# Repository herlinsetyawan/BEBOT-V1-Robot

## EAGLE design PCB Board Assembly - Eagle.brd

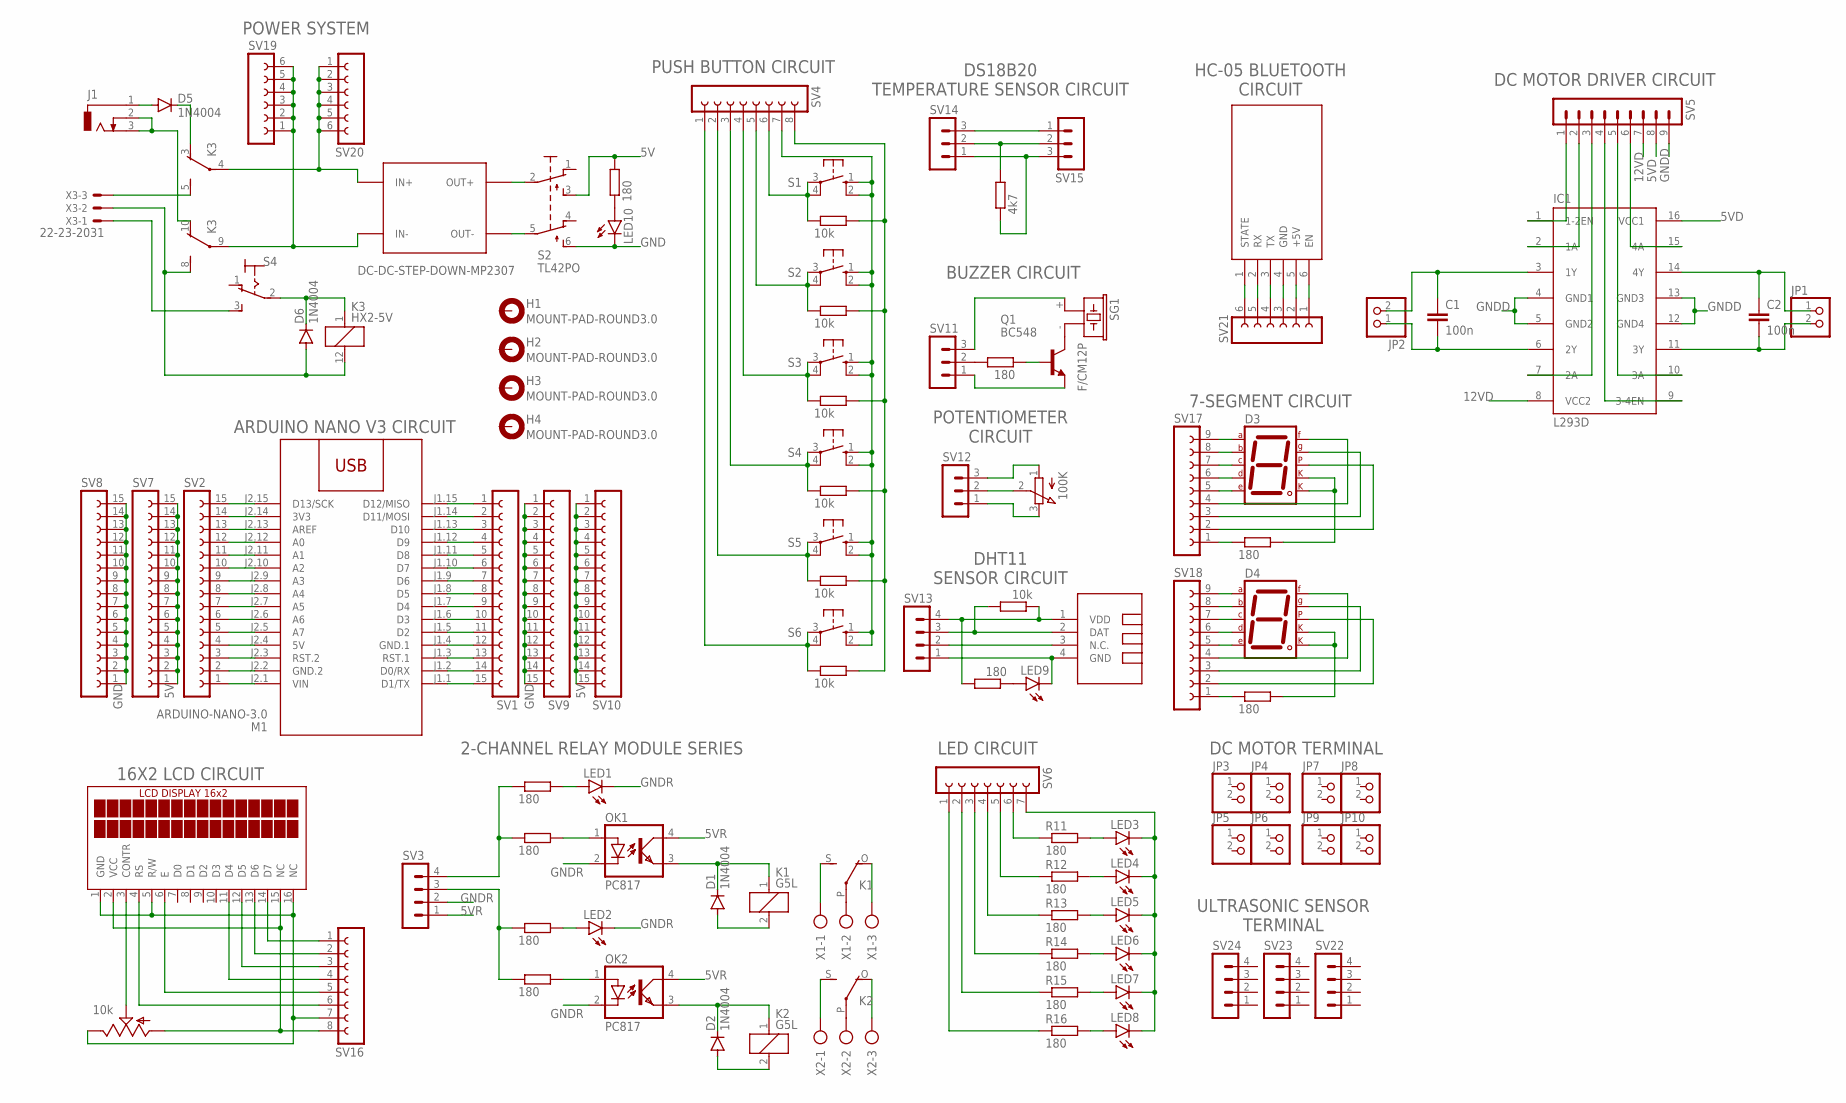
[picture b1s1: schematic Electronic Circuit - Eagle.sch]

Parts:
C1, C2: 100n; C050-024X044
D1, D2, D5, D6: 1N4004; DO41-10
D3, D4: 7SEG-CK; 7SEG-13
DIS1: TUXGR_16X2_R2
H1, H2, H3, H4: MOUNT-PAD-ROUND3.0; 3,0-PAD
IC1: L293D; DIL16
J1: DCJ0303
JP1, JP2, JP3, JP4, JP5, JP6, JP7, JP8, JP9, JP10: PINHD-1X2; 1X02
K1, K2: G5L; G5LE
K3: HX2-5V; HX
LED1, LED2, LED3, LED4, LED5, LED6, LED7, LED8, LED9, LED10: LED3MM
M1: ARDUINO-NANO-3.0
OK1, OK2: PC817; DIL04
Q1: BC548; TO92-EBC
R1, R2, R3, R4, R11, R12, R13, R14, R15, R16, R17, R20, R23, R24, R25: 180; 0204/7
R5, R6, R7, R8, R9, R10, R19: 10k; 0204/7
R18: 100K; EVUF
R21: 4k7; 0204/7
R22: 10k; CA6V
S1, S3, S5, S6, S7, S8: 10-XX; B3F-10XX
S2: TL42PO; TL4XPO
S4: M9040P
SG1: F/CM12P
SV1, SV2, SV7, SV8, SV9, SV10: FE15-1; FE15
SV3, SV13, SV22, SV23, SV24: MA04-1
SV4, SV16: FE08-1; FE08
SV5: MA09-1
SV6: FE07-1; FE07
SV11, SV12, SV14, SV15: MA03-1
SV17, SV18: FE09-1; FE09
SV19, SV20, SV21: FE06-1; FE06
U$1: TEMP-HUM-SENSOR-DHT11
U$2: WIRELESS-BLUETOOTH-HC-05
U$3: DC-DC-STEP-DOWN-MP2307
X1, X2: AK500/3
X3: 22-23-2031

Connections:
5V: R25.2, S2.3 (S), SV7.1, SV7.2, SV7.3, SV7.4, SV7.5, SV7.6, SV7.7, SV7.8, SV7.9, SV7.10, SV7.11, SV7.12, SV7.13, SV7.14, SV7.15, SV10.1, SV10.2, SV10.3, SV10.4, SV10.5, SV10.6, SV10.7, SV10.8, SV10.9, SV10.10, SV10.11, SV10.12, SV10.13, SV10.14, SV10.15
5VD: IC1.16 (VCC1), SV5.8
5VR: OK1.4 (COL), OK2.4 (COL), SV3.1
12VD: IC1.8 (VCC2), SV5.7
GND: LED10.K (C), S2.6 (S1), SV8.1, SV8.2, SV8.3, SV8.4, SV8.5, SV8.6, SV8.7, SV8.8, SV8.9, SV8.10, SV8.11, SV8.12, SV8.13, SV8.14, SV8.15, SV9.1, SV9.2, SV9.3, SV9.4, SV9.5, SV9.6, SV9.7, SV9.8, SV9.9, SV9.10, SV9.11, SV9.12, SV9.13, SV9.14, SV9.15
GNDD: IC1.4 (GND1), IC1.5 (GND2), IC1.12 (GND4), IC1.13 (GND3), SV5.9
GNDR: LED1.K (C), LED2.K (C), OK1.2 (C), OK2.2 (C), SV3.2
unnamed: M1.J2.15 (D13/SCK), SV2.15
unnamed: M1.J2.14 (3V3), SV2.14
unnamed: M1.J2.13 (AREF), SV2.13
unnamed: M1.J2.12 (A0), SV2.12
unnamed: M1.J2.11 (A1), SV2.11
unnamed: M1.J2.10 (A2), SV2.10
unnamed: M1.J2.9 (A3), SV2.9
unnamed: M1.J2.8 (A4), SV2.8
unnamed: M1.J2.7 (A5), SV2.7
unnamed: M1.J2.6 (A6), SV2.6
unnamed: M1.J2.5 (A7), SV2.5
unnamed: M1.J2.4 (5V), SV2.4
unnamed: M1.J2.3 (RST.2), SV2.3
unnamed: M1.J2.2 (GND.2), SV2.2
unnamed: M1.J2.1 (VIN), SV2.1
unnamed: M1.J1.1 (D1/TX), SV1.15
unnamed: M1.J1.2 (D0/RX), SV1.14
unnamed: M1.J1.3 (RST.1), SV1.13
unnamed: M1.J1.4 (GND.1), SV1.12
unnamed: M1.J1.5 (D2), SV1.11
unnamed: M1.J1.6 (D3), SV1.10
unnamed: M1.J1.7 (D4), SV1.9
unnamed: M1.J1.8 (D5), SV1.8
unnamed: M1.J1.9 (D6), SV1.7
unnamed: M1.J1.10 (D7), SV1.6
unnamed: M1.J1.11 (D8), SV1.5
unnamed: M1.J1.12 (D9), SV1.4
unnamed: M1.J1.13 (D10), SV1.3
unnamed: M1.J1.14 (D11/MOSI), SV1.2
unnamed: M1.J1.15 (D12/MISO), SV1.1
unnamed: OK1.1 (A), R1.2
unnamed: D1.C, K1.1, OK1.3 (EMIT)
unnamed: D1.A, K1.2
unnamed: K1.S, X1.1
unnamed: K1.P, X1.2
unnamed: K1.O, X1.3
unnamed: OK2.1 (A), R2.2
unnamed: D2.C, K2.1, OK2.3 (EMIT)
unnamed: D2.A, K2.2
unnamed: K2.S, X2.1
unnamed: K2.P, X2.2
unnamed: K2.O, X2.3
unnamed: R2.1, R4.1, SV3.3
unnamed: R1.1, R3.1, SV3.4
unnamed: LED1.A, R3.2
unnamed: LED2.A, R4.2
unnamed: C1.1, IC1.3 (1Y), JP2.2
unnamed: C1.2, IC1.6 (2Y), JP2.1
unnamed: C2.1, IC1.14 (4Y), JP1.1
unnamed: C2.2, IC1.11 (3Y), JP1.2
unnamed: IC1.1 (1-2EN), SV5.1
unnamed: IC1.2 (1A), SV5.2
unnamed: IC1.7 (2A), SV5.3
unnamed: IC1.9 (3-4EN), SV5.4
unnamed: IC1.10 (3A), SV5.5
unnamed: IC1.15 (4A), SV5.6
unnamed: R5.1, S1.3, S1.4 (P1), SV4.6
unnamed: R6.1, S3.3, S3.4 (P1), SV4.5
unnamed: R7.1, S5.3, S5.4 (P1), SV4.4
unnamed: R8.1, S6.3, S6.4 (P1), SV4.3
unnamed: R9.1, S7.3, S7.4 (P1), SV4.2
unnamed: R10.1, S8.3, S8.4 (P1), SV4.1
unnamed: S1.1 (S), S1.2 (S1), S3.1 (S), S3.2 (S1), S5.1 (S), S5.2 (S1), S6.1 (S), S6.2 (S1), S7.1 (S), S7.2 (S1), S8.1 (S), S8.2 (S1), SV4.7
unnamed: R5.2, R6.2, R7.2, R8.2, R9.2, R10.2, SV4.8
unnamed: LED3.A, R11.2
unnamed: LED4.A, R12.2
unnamed: LED5.A, R13.2
unnamed: LED6.A, R14.2
unnamed: LED7.A, R15.2
unnamed: LED8.A, R16.2
unnamed: LED3.K (C), LED4.K (C), LED5.K (C), LED6.K (C), LED7.K (C), LED8.K (C), SV6.7
unnamed: R11.1, SV6.6
unnamed: R12.1, SV6.5
unnamed: R13.1, SV6.4
unnamed: R14.1, SV6.3
unnamed: R15.1, SV6.2
unnamed: R16.1, SV6.1
unnamed: SG1.+ (1), SV11.3
unnamed: Q1.E, SV11.1
unnamed: Q1.C, SG1.- (2)
unnamed: Q1.B, R17.2
unnamed: R17.1, SV11.2
unnamed: R18.2 (S), SV12.2
unnamed: R18.1 (A), SV12.3
unnamed: R18.3 (E), SV12.1
unnamed: R19.1, R20.2, SV13.4, U$1.1 (VDD)
unnamed: R19.2, SV13.3, U$1.2 (DAT)
unnamed: SV13.2, U$1.3 (N.C.)
unnamed: SV14.3, SV15.1
unnamed: LED9.K (C), SV13.1, U$1.4 (GND)
unnamed: R21.2, SV14.2, SV15.2
unnamed: LED9.A, R20.1
unnamed: R21.1, SV14.1, SV15.3
unnamed: DIS1.1 (GND), DIS1.5 (R/W), DIS1.16 (NC), R22.E, SV16.7
unnamed: DIS1.2 (VCC), DIS1.15 (NC), R22.A, SV16.8
unnamed: DIS1.3 (CONTR), R22.S
unnamed: DIS1.14 (D7), SV16.1
unnamed: DIS1.13 (D6), SV16.2
unnamed: DIS1.12 (D5), SV16.3
unnamed: DIS1.11 (D4), SV16.4
unnamed: DIS1.6 (E), SV16.5
unnamed: DIS1.4 (RS), SV16.6
unnamed: R23.1, SV17.1
unnamed: D3.3 (CK1), D3.8 (CK2), R23.2
unnamed: D3.7 (A), SV17.9
unnamed: D3.6 (B), SV17.8
unnamed: D3.4 (C), SV17.7
unnamed: D3.2 (D), SV17.6
unnamed: D3.1 (E), SV17.5
unnamed: D3.9 (F), SV17.4
unnamed: D3.10 (G), SV17.3
unnamed: D3.5 (DP), SV17.2
unnamed: R24.1, SV18.1
unnamed: D4.3 (CK1), D4.8 (CK2), R24.2
unnamed: D4.7 (A), SV18.9
unnamed: D4.6 (B), SV18.8
unnamed: D4.4 (C), SV18.7
unnamed: D4.2 (D), SV18.6
unnamed: D4.1 (E), SV18.5
unnamed: D4.9 (F), SV18.4
unnamed: D4.10 (G), SV18.3
unnamed: D4.5 (DP), SV18.2
unnamed: S2.2, U$3.OUT+
unnamed: S2.5 (P1), U$3.OUT-
unnamed: LED10.A, R25.1
unnamed: SV21.1, U$2.6 (EN)
unnamed: SV21.2, U$2.5 (+5V)
unnamed: D6.C, K3.1, S4.2
unnamed: D5.A, J1.1
unnamed: J1.2, J1.3, K3.10 (O)
unnamed: D5.C, K3.3 (O)
unnamed: K3.5 (S), X3.3
unnamed: D6.A, K3.8 (S), K3.12 (2), X3.2
unnamed: S4.3 (S), X3.1
unnamed: K3.9, SV19.1, SV19.2, SV19.3, SV19.4, SV19.5, SV19.6, U$3.IN-
unnamed: K3.4, SV20.1, SV20.2, SV20.3, SV20.4, SV20.5, SV20.6, U$3.IN+
unnamed: SV21.3, U$2.4 (GND)
unnamed: SV21.4, U$2.3 (TX)
unnamed: SV21.5, U$2.2 (RX)
unnamed: SV21.6, U$2.1 (STATE)

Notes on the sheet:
POWER SYSTEM
PUSH BUTTON CIRCUIT
ARDUINO NANO V3 CIRCUIT
DS18B20 TEMPERATURE SENSOR CIRCUIT
BUZZER CIRCUIT
POTENTIOMETER CIRCUIT
DHT11 SENSOR CIRCUIT
HC-05 BLUETOOTH CIRCUIT
2-CHANNEL RELAY MODULE SERIES
DC MOTOR DRIVER CIRCUIT
7-SEGMENT CIRCUIT
LED CIRCUIT
DC MOTOR TERMINAL
ULTRASONIC SENSOR TERMINAL
16X2 LCD CIRCUIT

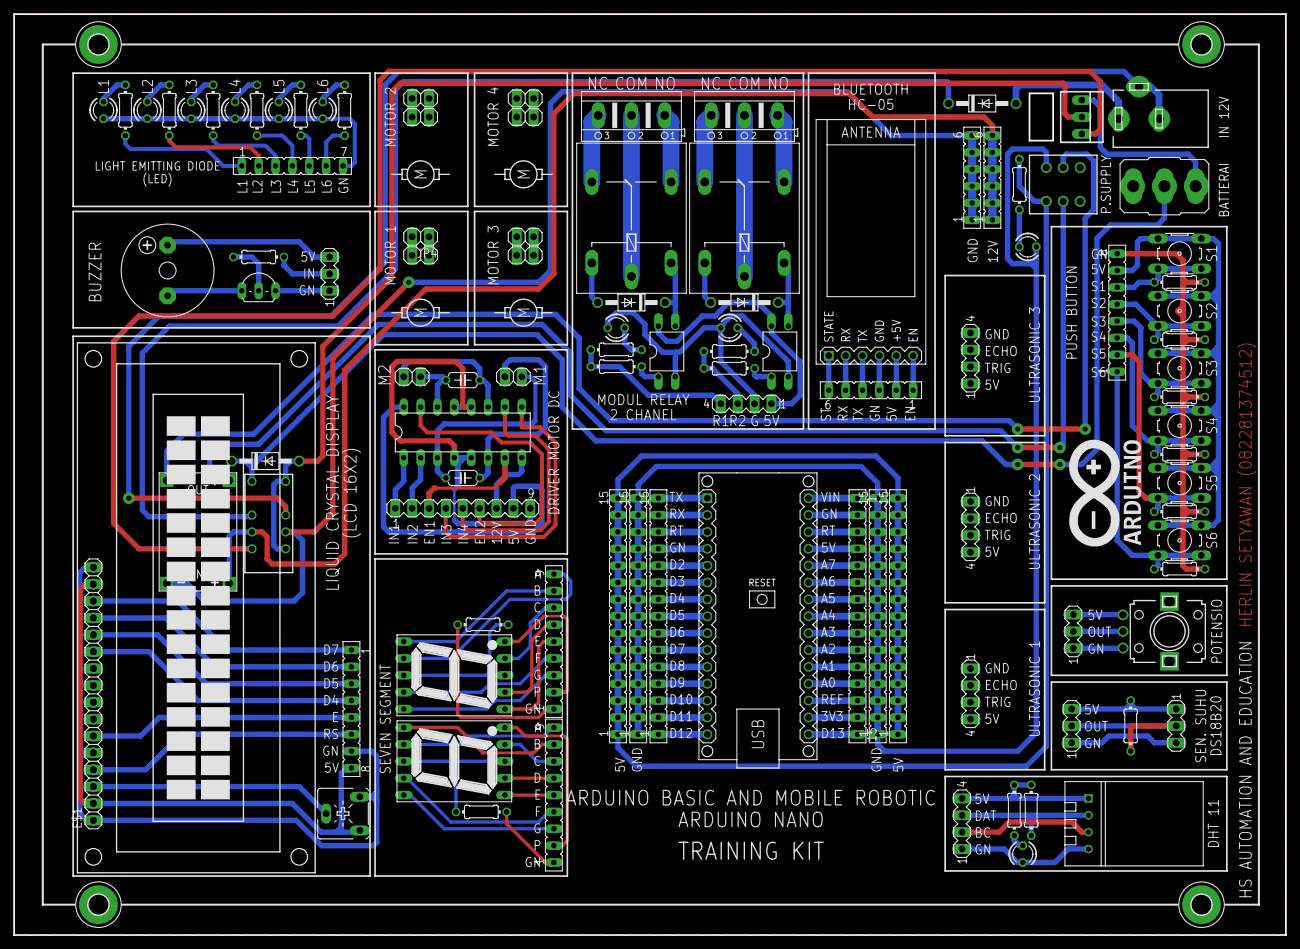
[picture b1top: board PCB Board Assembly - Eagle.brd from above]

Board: 2 copper layers, 191.5 x 138.7 mm, 107 parts (0 on the bottom side), 147 nets.

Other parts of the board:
E$1: 1X16

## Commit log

2025-09-15 Create Build

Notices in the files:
parts and their libraries:
Arduino dan Step Down: Released under the Creative Commons Attribution 4.0 International License: http://creativecommons.org/licenses/by/4.0
